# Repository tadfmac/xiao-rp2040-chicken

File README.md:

# xiao-rp2040-chicken

A crazy midi controller make with Seeed Studio's [XIAO RP2040](https://www.seeedstudio.com/XIAO-RP2040-v1-0-p-5026.html)  and showting chicken!

### schematics

### parts list

- [XIAO RP2040](https://www.seeedstudio.com/XIAO-RP2040-v1-0-p-5026.html) x 1
- [Mic board](https://akizukidenshi.com/catalog/g/gM-08940/) x 1
- [Vibration sensor](https://akizukidenshi.com/catalog/g/gP-15375/) x 1
- 2.54mm pitch lowprofile pinheader (1x7) x 2
- 0805 10kΩ resistor x 1
- 2.54mm pitch L-angle pinsocket (1x4) x 1
- showting chicken (**Important! the showting checken must 40cm or larger! it maybe cannot insert to smaller it.**) [example (must chose '40cm')](https://ja.aliexpress.com/item/32899623947.html?spm=a2g0o.productlist.0.0.47ca4900kHPyQw&algo_pvid=134d390f-c75f-4f2b-b0bf-b81694eb1b31&algo_exp_id=134d390f-c75f-4f2b-b0bf-b81694eb1b31-18&pdp_ext_f=%7B"sku_id"%3A"65853772185"%7D&pdp_npi=2%40dis%21JPY%21656.0%21525.0%21%21%21%21%21%402103250d16615813887934542e5813%2165853772185%21sea&curPageLogUid=4S6EgBV8VM1s) 

### How to Making?

1. Read the [mic board instructions (japanese)](https://akizukidenshi.com/download/ds/akizuki/AE-SPU0414.pdf) and set the mic gain on the mic board to 20db. Solder to the jumper part of the board.
2. Solder the parts while looking at the schematic. For thinness, please use low profile pin headers to connect the board and XIAO RP2040.
3. Connect the USB cable to XIAO RP2040.
4. Insert the board with soldered components through the mouth of the chicken. It's hard to insert, but do your best!

### XIAO RP2040 Programming

1. Use Arduino. First, have the [Arduino IDE](https://www.arduino.cc/en/software) installed on your PC.
2. Next, install the software for XIAO RP2040 on Arduino by [Seeed Studio's instructions (Seeed Studio XIAO RP2040 with Arduino)](https://wiki.seeedstudio.com/XIAO-RP2040-with-Arduino/).
3. Finally, download [XIAO-RP2040-CHICKEN.ino](https://gist.github.com/tadfmac/8916deed75f60839810058b9485af5d4) and flash it from your Arduino IDE to your XIAO RP2040.
4. done! Let's Enjoy with connect through USB your PC and start your MIDI software.

### License

MIT

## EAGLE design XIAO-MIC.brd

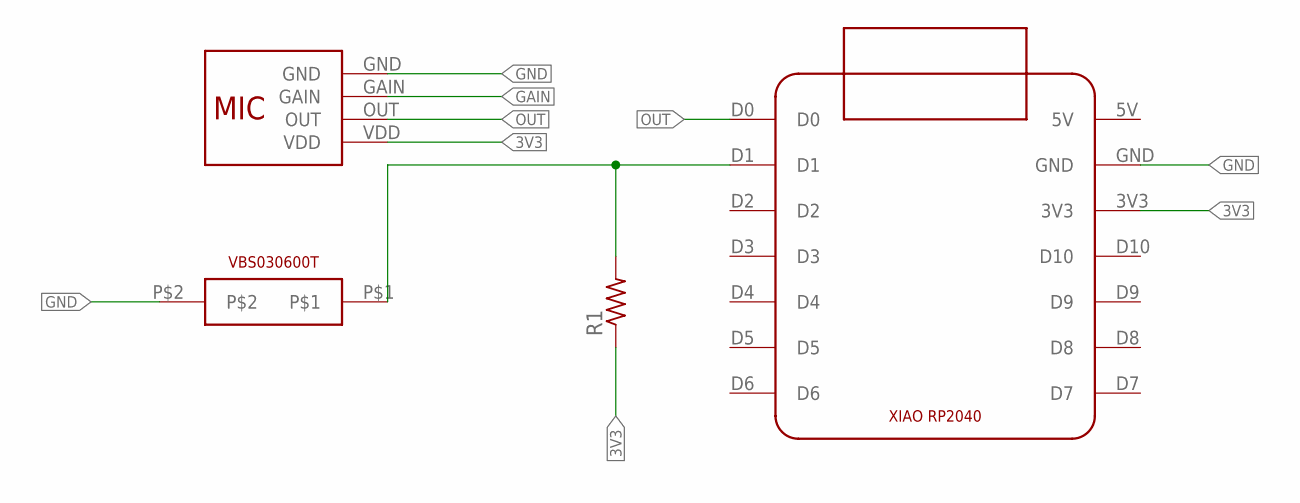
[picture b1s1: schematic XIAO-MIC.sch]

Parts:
R1: R-US_R0805; R0805
U$1: MEMS-MIC; MEMS-MIC-LANGLE
U$2: VBS030600T
U$3: XIAO-RP2040

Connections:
3V3: R1.1, U$1.VDD, U$3.3V3
GAIN: U$1.GAIN
GND: U$1.GND, U$2.P$2, U$3.GND
unnamed: R1.2, U$2.P$1, U$3.D1
OUT: U$1.OUT, U$3.D0

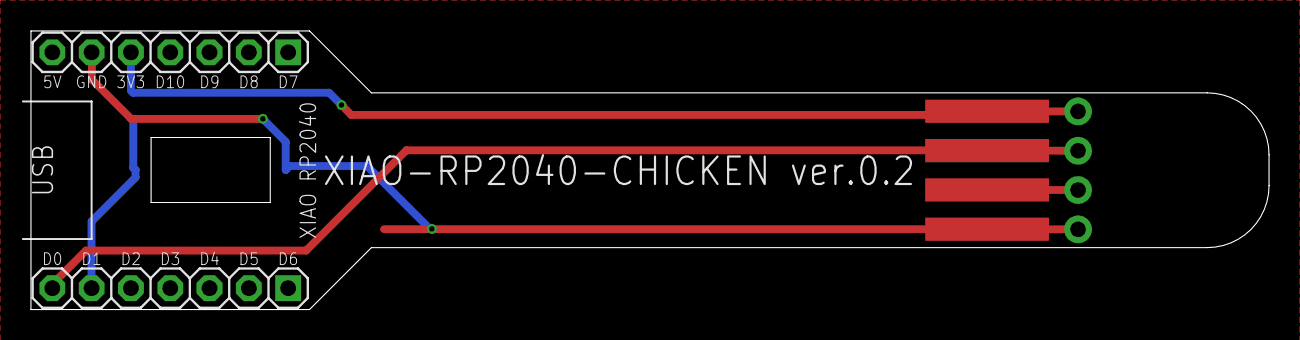
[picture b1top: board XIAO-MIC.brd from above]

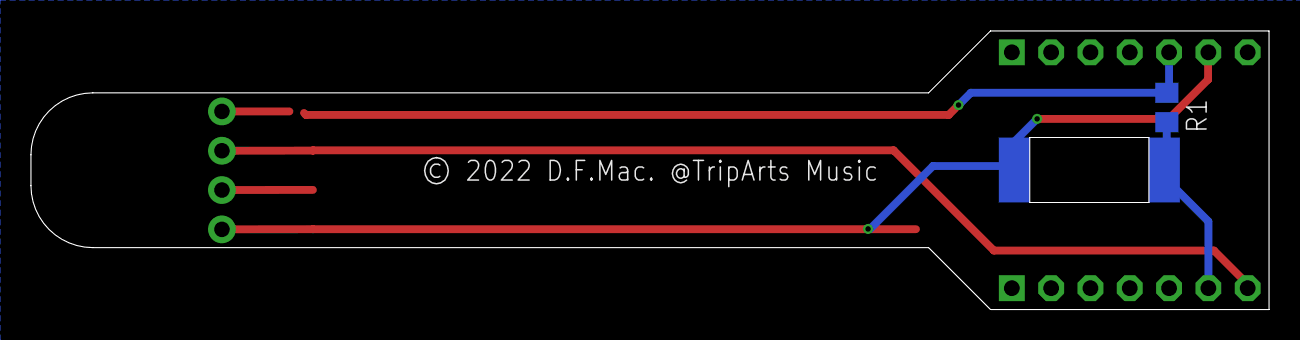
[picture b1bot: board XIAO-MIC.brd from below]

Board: 2 copper layers, 80.0 x 18.0 mm, 4 parts (2 on the bottom side), 4 nets.

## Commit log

2022-08-27 remove .DS_Store
2022-08-27 fix silk typo and renew readme.md
2022-09-01 remove camoutput folder

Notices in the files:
XIAO-MIC.brd:
© 2022 D.F.Mac. @TripArts Music
XIAO-MIC.sch:
©︎2022 by D.F.Mac.@TripArts Music
